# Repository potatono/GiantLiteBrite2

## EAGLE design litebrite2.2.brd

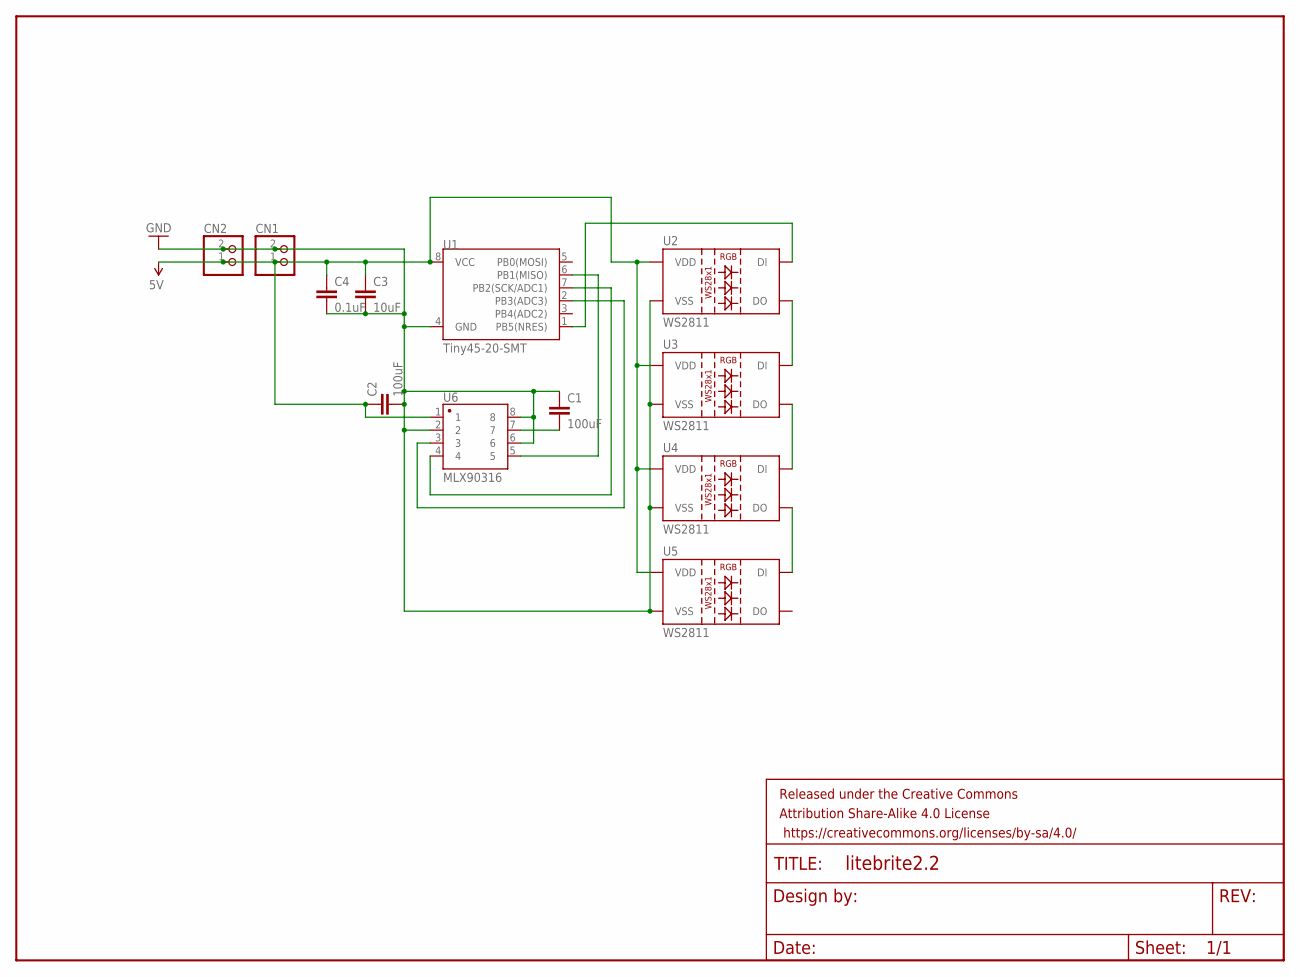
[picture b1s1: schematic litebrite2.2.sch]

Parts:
C1, C2: 100uF; 1210
C3: 10uF; 1206
C4: 0.1uF; 0402-CAP
CN1, CN2: JST_2PIN-SMT-RA; JST-PH-2-SMT-RA
FRAME1: FRAME-LETTERNO_PACKAGE; DUMMY
U1: Tiny45-20-SMT; SO08-EIAJ
U2, U3, U4, U5: WS2811; LED-TRICOLOR-5050-IC
U6: MLX90316; SO08

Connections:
5V: C2.1, C3.1, C4.1, CN1.1 (2), CN2.1 (2), U1.8 (VCC), U2.3 (VDD), U2.5 (VDD), U3.3 (VDD), U3.5 (VDD), U4.3 (VDD), U4.5 (VDD), U5.3 (VDD), U5.5 (VDD), U6.1
GND: C1.1, C2.2, C3.2, C4.2, CN1.2 (1), CN2.2 (1), U1.4 (GND), U2.6 (VSS), U3.6 (VSS), U4.6 (VSS), U5.6 (VSS), U6.2, U6.6, U6.8
unnamed: U2.1 (DO), U3.2 (DI)
unnamed: U3.1 (DO), U4.2 (DI)
unnamed: U4.1 (DO), U5.2 (DI)
unnamed: U1.1 (PB5(NRES)), U2.2 (DI)
unnamed: C1.2, U6.7
unnamed: U1.6 (PB1(MISO)), U6.5
unnamed: U1.7 (PB2(SCK/ADC1)), U6.4
unnamed: U1.2 (PB3(ADC3)), U6.3

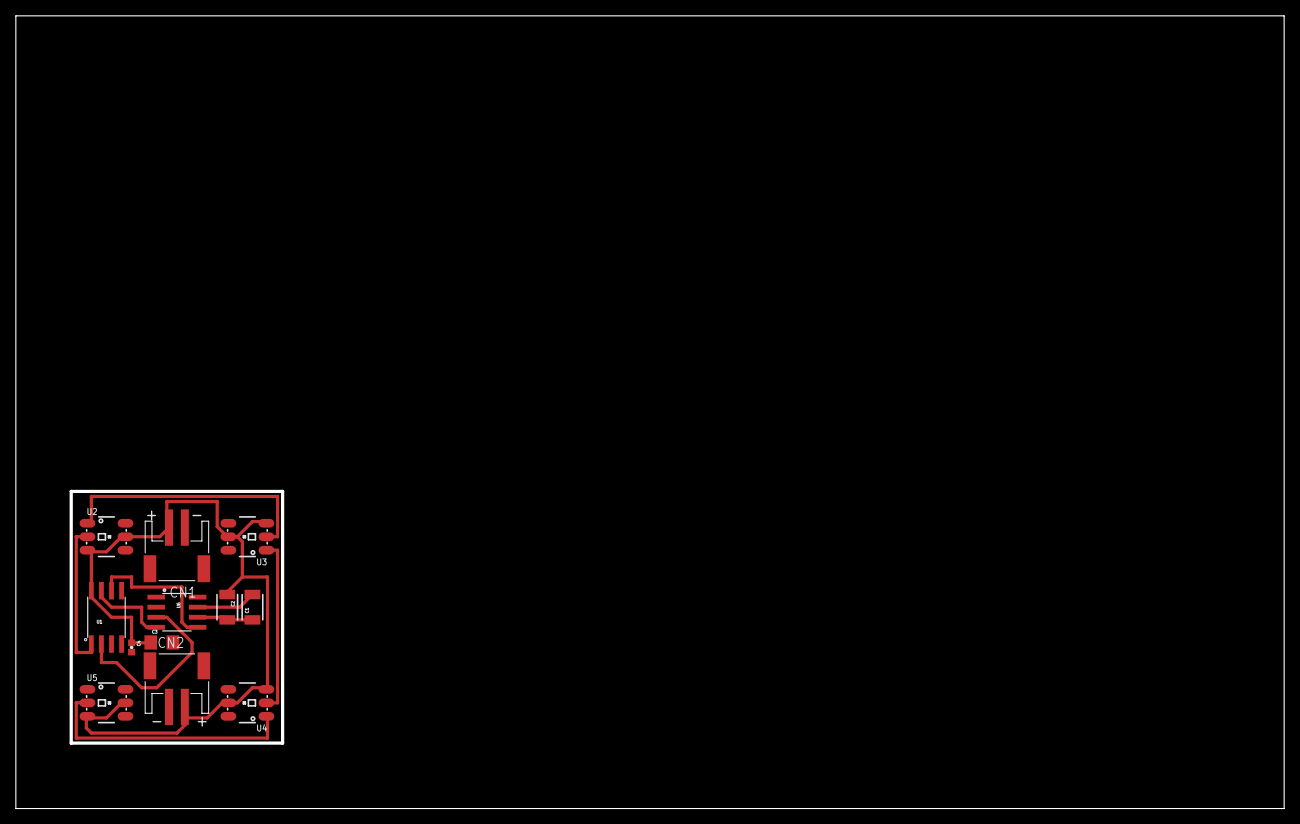
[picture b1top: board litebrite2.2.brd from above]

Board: 2 copper layers, 160.0 x 100.0 mm, 13 parts (0 on the bottom side), 10 nets.

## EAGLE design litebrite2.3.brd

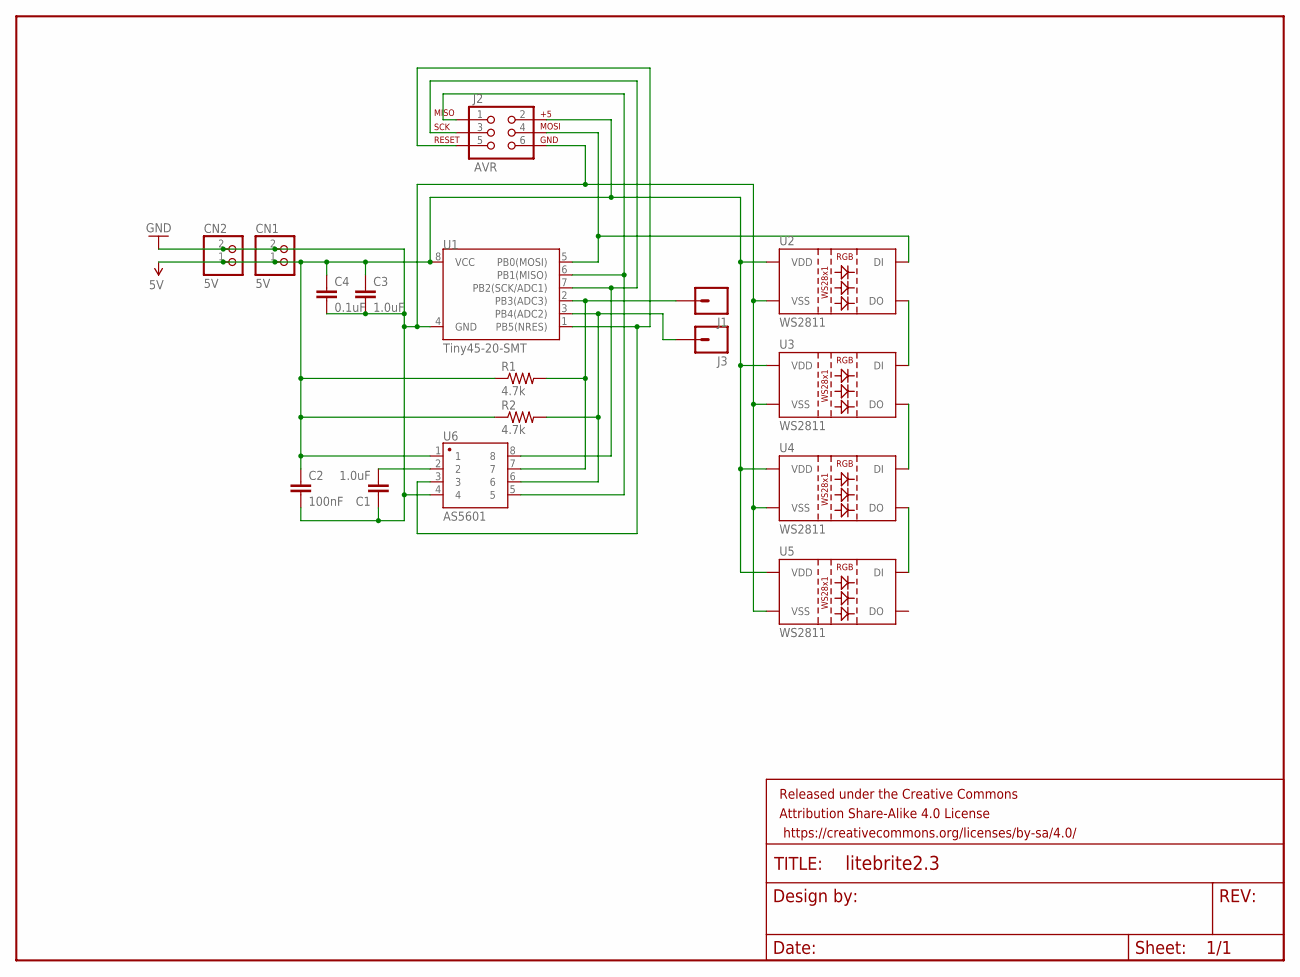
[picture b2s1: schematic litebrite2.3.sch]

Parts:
C1, C3: 1.0uF; 0402-CAP
C2: 100nF; 0402-CAP
C4: 0.1uF; 0402-CAP
CN1, CN2: 5V; JST-PH-2-SMT-RA
FRAME1: FRAME-LETTERNO_PACKAGE; DUMMY
J1, J3: M01SMD; LUXEON-PAD
J2: AVR; 2X3
R1, R2: 4.7k; 0603-RES
U1: Tiny45-20-SMT; SO08-EIAJ
U2, U3, U4, U5: WS2811; LED-TRICOLOR-5050-IC
U6: AS5601; SO08

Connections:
5V: C2.1, C3.1, C4.1, CN1.1 (2), CN2.1 (2), J2.2, R1.1, R2.1, U1.8 (VCC), U2.3 (VDD), U2.5 (VDD), U3.3 (VDD), U3.5 (VDD), U4.3 (VDD), U4.5 (VDD), U5.3 (VDD), U5.5 (VDD), U6.1
GND: C1.1, C2.2, C3.2, C4.2, CN1.2 (1), CN2.2 (1), J2.6, U1.4 (GND), U2.6 (VSS), U3.6 (VSS), U4.6 (VSS), U5.6 (VSS), U6.4
unnamed: U2.1 (DO), U3.2 (DI)
unnamed: U3.1 (DO), U4.2 (DI)
unnamed: U4.1 (DO), U5.2 (DI)
unnamed: J2.4, U1.5 (PB0(MOSI)), U2.2 (DI)
unnamed: J3.P$1, R2.2, U1.3 (PB4(ADC2)), U6.6
unnamed: J1.P$1, R1.2, U1.2 (PB3(ADC3)), U6.7
unnamed: J2.3, U1.7 (PB2(SCK/ADC1)), U6.8
unnamed: J2.1, U1.6 (PB1(MISO)), U6.5
unnamed: J2.5, U1.1 (PB5(NRES)), U6.3
unnamed: C1.2, U6.2

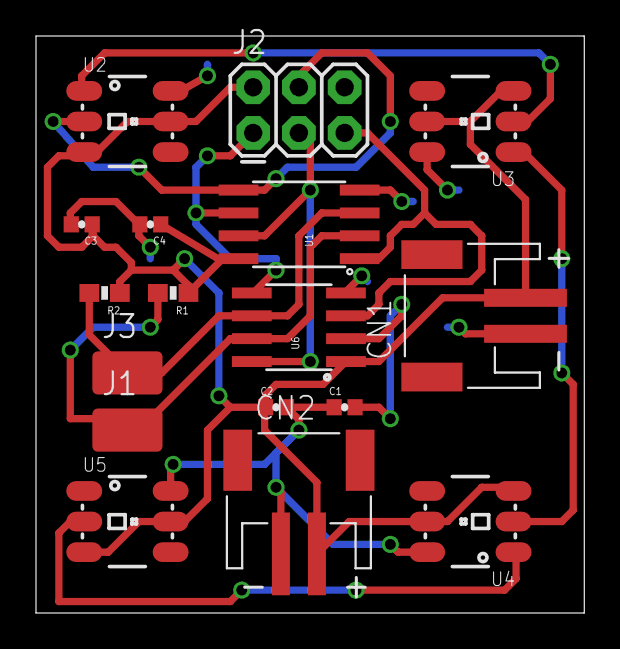
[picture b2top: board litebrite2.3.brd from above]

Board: 2 copper layers, 30.5 x 32.1 mm, 18 parts (0 on the bottom side), 12 nets.

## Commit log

2016-02-19 clean up

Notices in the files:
parts and their libraries:
SparkFun-DigitalIC: Licensing: Creative Commons ShareAlike 4.0 International - https://creativecommons.org/licenses/by-sa/4.0
SparkFun-Aesthetics: Released under the Creative Commons Attribution Share-Alike 4.0 License
SparkFun-Aesthetics: https://creativecommons.org/licenses/by-sa/4.0
